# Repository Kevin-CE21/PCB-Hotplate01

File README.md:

# PCB Hotplate Project (KiCad)
## PCB Layout:

## Schematic: 

## 3D Model:

## Overview

This project is a custom designed PCB hotplate for reflow soldering, built around an Arduino Nano. The board reads real time temperature through an analog LMT85 sensor and displays live readings on an I2C OLED screen, with two push buttons for user control. The heating element is not a discrete part. It is the copper PCB trace itself, laid out in a serpentine pattern across roughly 3.4 meters of 1.3 mm wide, 1 oz copper. At room temperature that trace measures about 1.3 ohms, which would pull over 9 A at 12 V if driven at full duty cycle. Since copper resistance rises with temperature, the trace is self limiting: current settles toward 5 to 6 A as it heats past 200 degrees C. Heating is switched using a low side IRFB7545 power MOSFET, driven through a PN2222A transistor for proper gate level switching, with Schottky diode protection and bulk capacitance across the power rail to maintain stability during high current switching events. Firmware manages duty cycle to stay within the 5 A fuse and supply rating, especially during the cold start ramp.

## Objectives

Design schematic in KiCad

Create custom PCB layout with the heating element integrated directly into copper

Handle higher current safely across a wide range of trace resistance as it heats

Separate power and control sections

Apply proper trace width for the heating load and calculate expected current draw

## Tools Used

KiCad

ERC and DRC checks

PCB layout editor

3D viewer

## System Design

The board includes:

Power input section

Heating element output

Control circuit

Switching device (MOSFET or transistor)

Protection components

Power traces are wider to handle higher current.
Signal traces are separated to reduce noise.

## Design Considerations

Calculated trace width based on expected current

Added thermal relief on pads

Placed high current components close together

Kept control logic isolated from heating path

Used ground plane for stability

## Skills Demonstrated

Schematic capture

PCB layout design

Power electronics basics

Trace width calculation

Design rule verification

Component placement strategy

## What I Learned

Current affects trace width directly

Layout affects heat distribution

Component placement affects performance

ERC and DRC checks prevent costly mistakes

## Possible Improvements

Add temperature sensor feedback

Add PID temperature control

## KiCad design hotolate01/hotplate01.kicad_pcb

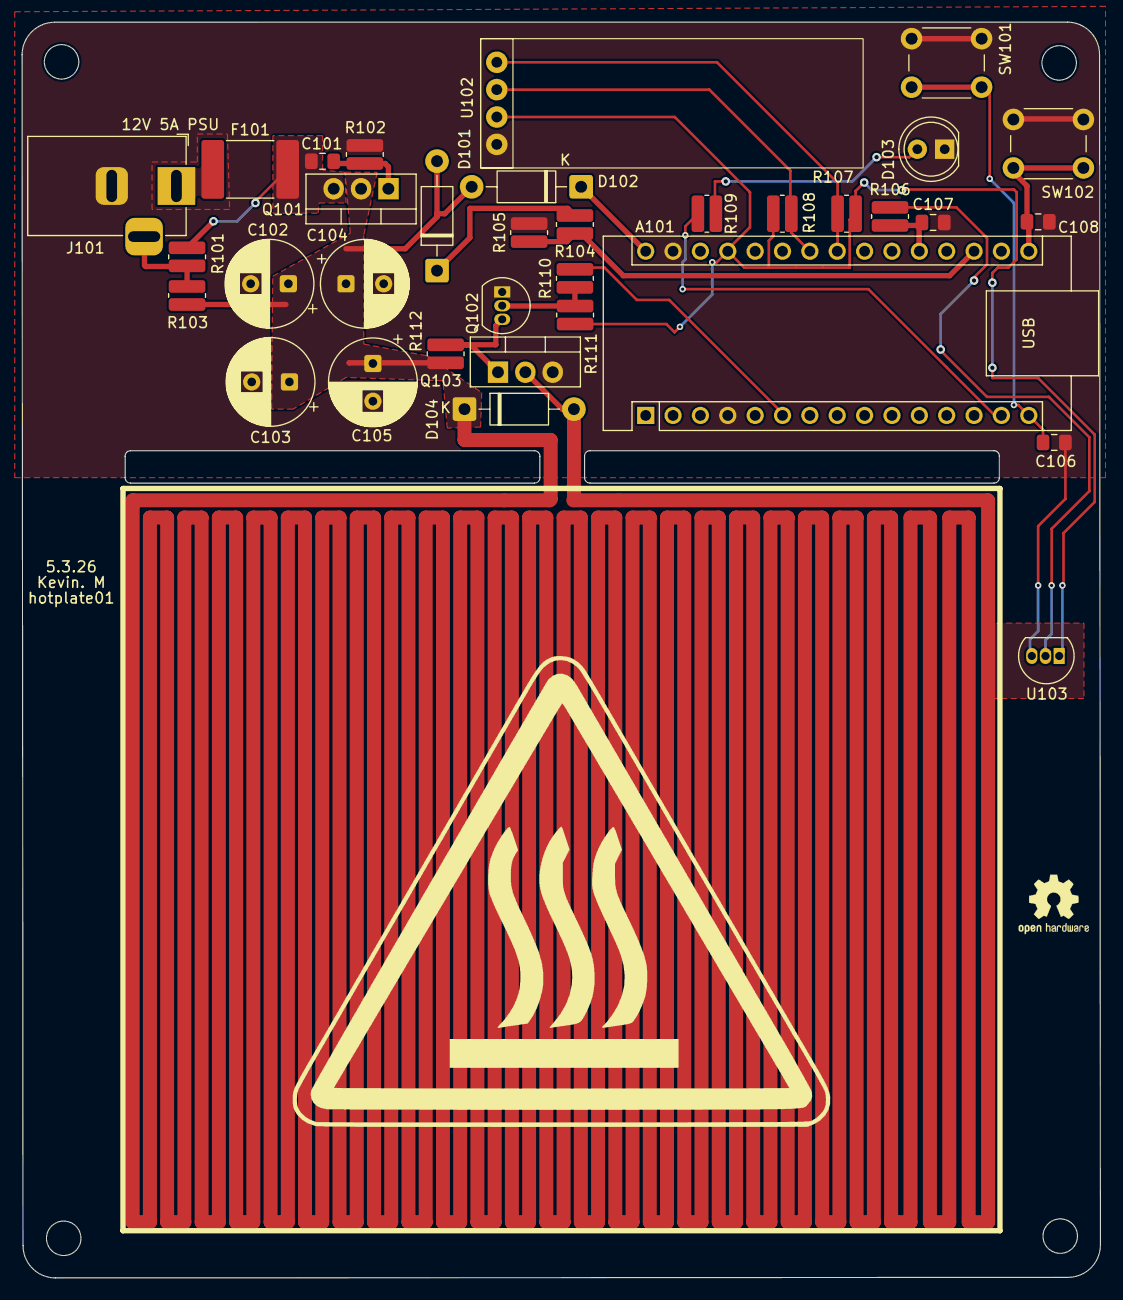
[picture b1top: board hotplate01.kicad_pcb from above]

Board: 2 copper layers, 100.1 x 116.6 mm, 36 parts (0 on the bottom side), 23 nets.

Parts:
A101: Arduino_Nano_v3.x; Arduino_Nano
C101: 10uF; C_0805_2012Metric_Pad1.18x1.45mm_HandSolder
C102, C103, C104, C105: 680uF; CP_Radial_D8.0mm_P3.50mm
C106, C107, C108: 100nF; C_0805_2012Metric_Pad1.18x1.45mm_HandSolder
D101, D102, D104: SB140; D_DO-41_SOD81_P10.16mm_Horizontal
D103: LED; LED_D5.0mm
F101: 5A; Fuse_2920_7451Metric_Pad2.10x5.45mm_HandSolder
J101: Barrel_Jack_Switch; BarrelJack_Horizontal
NT101, NT102: NetTie_2; NetTie-2_SMD_Pad1.3mm
Q101: IRF4905; TO-220-3_Vertical
Q102: PN2222A; TO-92_Inline
Q103: IRFB7545PBF; TO-220-3_Vertical
R101, R103: 47R; R_0612_1632Metric_Pad1.18x3.40mm_HandSolder
R102, R105, R106, R109, R111: 10k; R_0612_1632Metric_Pad1.18x3.40mm_HandSolder
R104: 70k; R_0612_1632Metric_Pad1.18x3.40mm_HandSolder
R107, R108, R112: 4k7; R_0612_1632Metric_Pad1.18x3.40mm_HandSolder
R110: 1k; R_0612_1632Metric_Pad1.18x3.40mm_HandSolder
SW101, SW102: SW_Push; SW_PUSH_6mm
U102: SSD1306 OLED 0.91; ssd1306oled0.91
U103: LMT85DCK; TO-92L_Inline

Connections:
+5V: A101.27 (+5V), R107.1, R108.1, R111.1, U102.3 (VCC), U103.1 (V_{DD})
/AREF: A101.18 (AREF), R104.2, R105.1
/GATE: A101.6 (D3), R110.1
/HOTPLATE: NT101.1, NT102.2
/LED: A101.14 (D11), R109.2
/SCL: A101.24 (A5), R108.2, U102.2 (SCL)
/SDA: A101.23 (A4), R107.2, U102.1 (SDA)
/SW1: A101.15 (D12), C106.1, SW101.2
/SW2: A101.16 (D13), C108.1, SW102.2
/TEMP: A101.20 (A1), C107.1, R106.1
GND: A101.4 (GND), A101.29 (GND), C102.2, C103.2, C104.2, C105.2, C106.2, C107.2, C108.2, D103.1 (K), J101.2, Q102.1 (E), Q103.3 (S), R102.2, R105.2, SW101.1, SW102.1, U102.4 (GND), U103.3 (GND)
unnamed: A101.30 (VIN), D102.1 (K)
unnamed: D101.1 (K), R104.1
unnamed: D103.2 (A), R109.1
unnamed: D104.2 (A), NT102.1, Q103.2 (D)
unnamed: F101.1, J101.1
unnamed: J101.3, R101.1, R103.1
unnamed: C101.1, F101.2, Q101.3 (S), R101.2
unnamed: C101.2, Q101.1 (G), R102.1
unnamed: Q102.2 (B), R110.2, R111.2
unnamed: Q102.3 (C), Q103.1 (G), R112.2
unnamed: R106.2, U103.2 (OUT)
VCC: C102.1, C103.1, C104.1, C105.1, D101.2 (A), D102.2 (A), D104.1 (K), NT101.2, Q101.2 (D), R103.2, R112.1

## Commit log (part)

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2026-05-04 Update images in README for PCB Hotplate Project
2026-05-04 Add 3D model section to README
    Add 3D model section to README with image.
2026-05-04 Reorder images in README for clarity
